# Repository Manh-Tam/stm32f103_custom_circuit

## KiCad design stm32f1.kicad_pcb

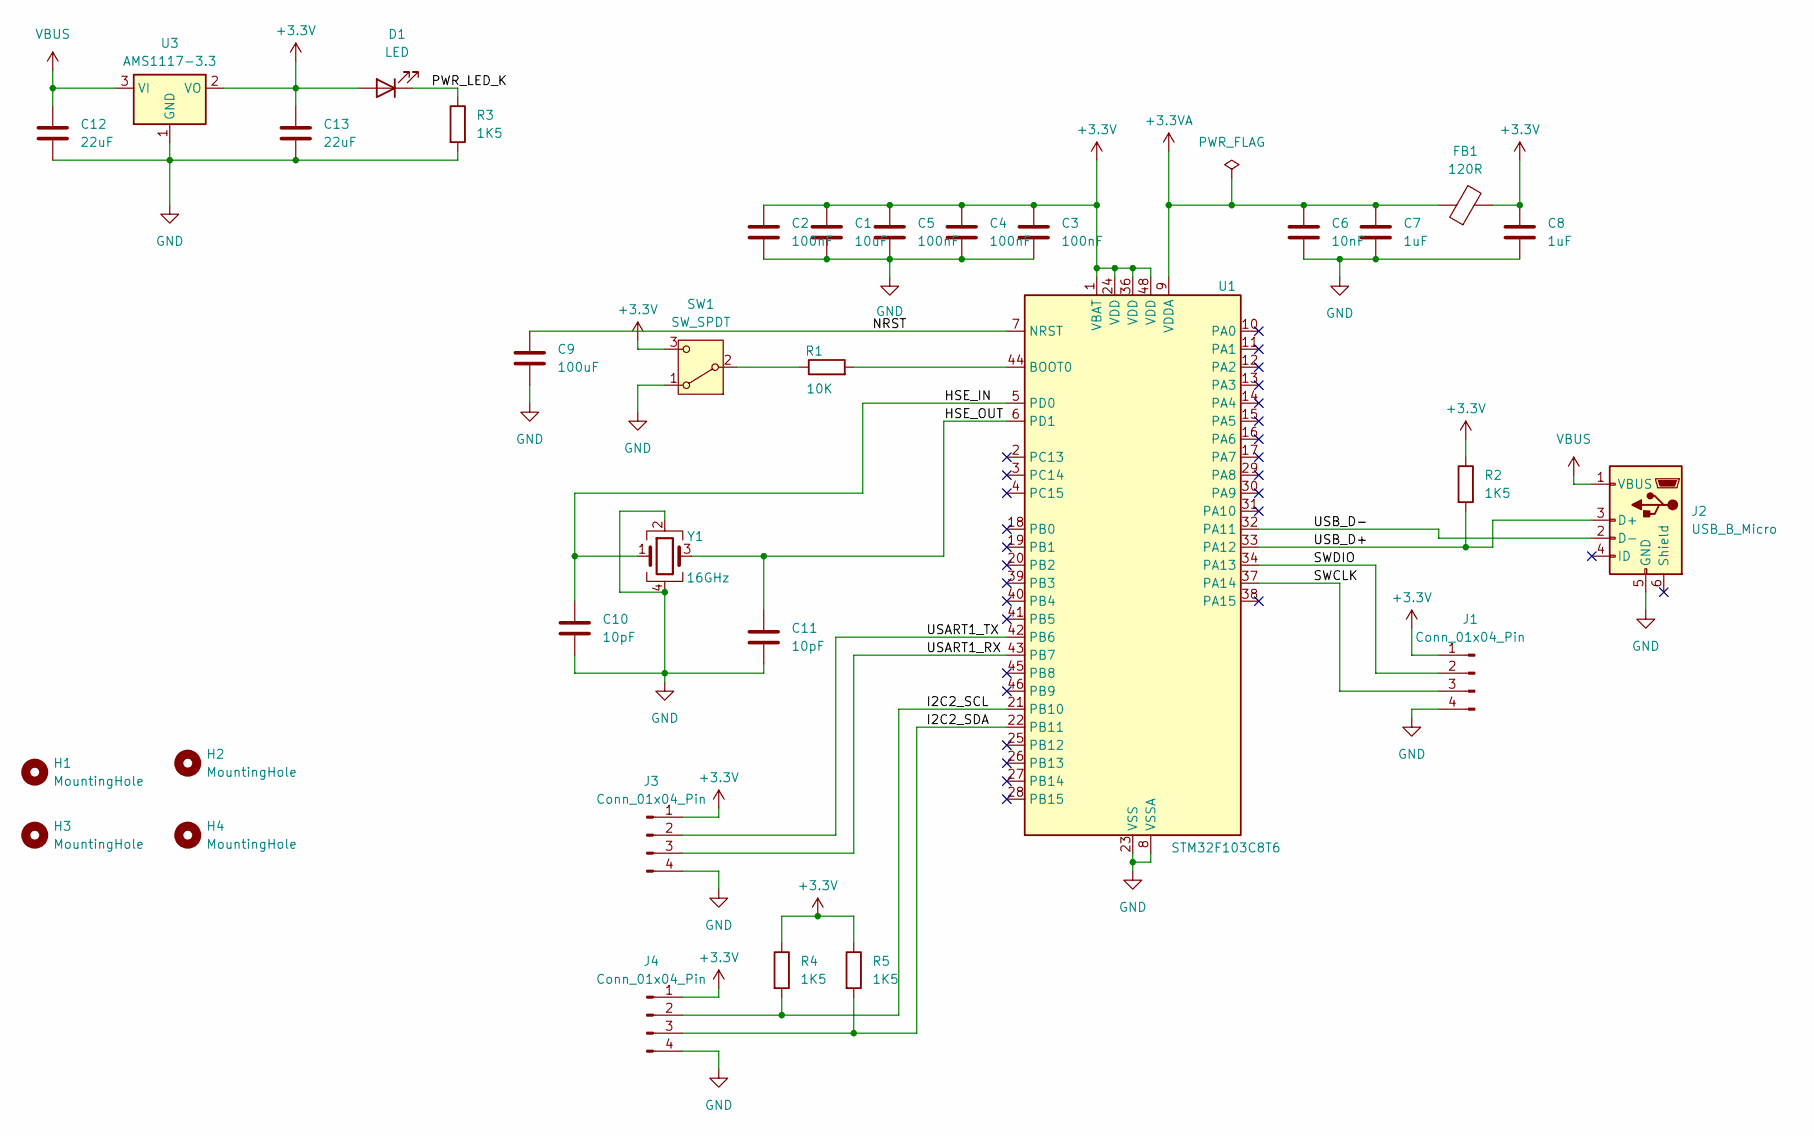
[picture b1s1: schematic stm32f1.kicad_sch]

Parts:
C1: 10uF; C_0402_1005Metric
C2, C3, C4, C5: 100nF; C_0402_1005Metric
C6: 10nF; C_0402_1005Metric
C7, C8: 1uF; C_0402_1005Metric
C9: 100uF; C_0402_1005Metric
C10, C11: 10pF; C_0402_1005Metric
C12, C13: 22uF; C_0805_2012Metric
D1: LED; LED_0603_1608Metric
FB1: 120R; L_0603_1608Metric
H1, H2, H3, H4: MountingHole; MountingHole_2.2mm_M2
J1, J3, J4: Conn_01x04_Pin; PinHeader_1x04_P2.54mm_Vertical
J2: USB_B_Micro; USB_Micro-B_Wuerth_629105150521
R1: 10K; R_0402_1005Metric
R2, R3, R4, R5: 1K5; R_0402_1005Metric
SW1: SW_SPDT; SW_SPDT_PCM12
U1: STM32F103C8T6; LQFP-48_7x7mm_P0.5mm
U3: AMS1117-3.3; SOT-223-3_TabPin2
Y1: 16GHz; Crystal_SMD_3225-4Pin_3.2x2.5mm

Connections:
+3.3V: C1.1, C2.1, C3.1, C4.1, C5.1, C8.1, C13.1, D1.2 (A), FB1.2, J1.1, J3.1, J4.1, R2.1, R4.1, R5.1, SW1.3 (C), U1.1 (VBAT), U1.24 (VDD), U1.36 (VDD), U1.48 (VDD), U3.2 (VO)
+3.3VA: C6.1, C7.1, FB1.1, U1.9 (VDDA)
/HSE_IN: C10.1, U1.5 (PD0), Y1.1
/HSE_OUT: C11.1, U1.6 (PD1), Y1.3
/I2C2_SCL: J4.2, R4.2, U1.21 (PB10)
/I2C2_SDA: J4.3, R5.2, U1.22 (PB11)
/NRST: C9.1, U1.7 (NRST)
/PWR_LED_K: D1.1 (K), R3.1
/SWCLK: J1.3, U1.37 (PA14)
/SWDIO: J1.2, U1.34 (PA13)
/USART1_RX: J3.3, U1.43 (PB7)
/USART1_TX: J3.2, U1.42 (PB6)
/USB_D+: J2.3 (D+), R2.2, U1.33 (PA12)
/USB_D-: J2.2 (D-), U1.32 (PA11)
GND: C1.2, C2.2, C3.2, C4.2, C5.2, C6.2, C7.2, C8.2, C9.2, C10.2, C11.2, C12.2, C13.2, J1.4, J2.5 (GND), J3.4, J4.4, R3.2, SW1.1 (A), U1.8 (VSSA), U1.23 (VSS), U1.35 (VSS), U1.47 (VSS), U3.1 (GND), Y1.2, Y1.4
unnamed: R1.1, SW1.2 (B)
unnamed: R1.2, U1.44 (BOOT0)
VBUS: C12.1, J2.1 (VBUS), U3.3 (VI)

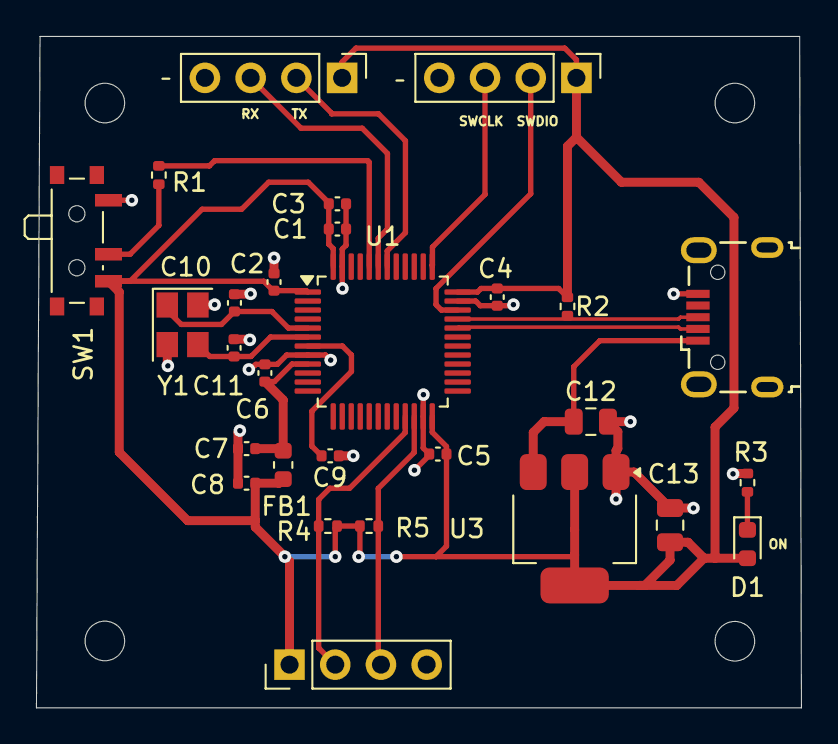
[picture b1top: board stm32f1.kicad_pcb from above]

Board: 2 copper layers, 42.5 x 37.3 mm, 32 parts (0 on the bottom side), 18 nets.

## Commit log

2025-03-24 done schematic circuit
2025-03-25 add pcb
